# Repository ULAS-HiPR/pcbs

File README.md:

# pcbs
Collection of all HiPR's PCB designs

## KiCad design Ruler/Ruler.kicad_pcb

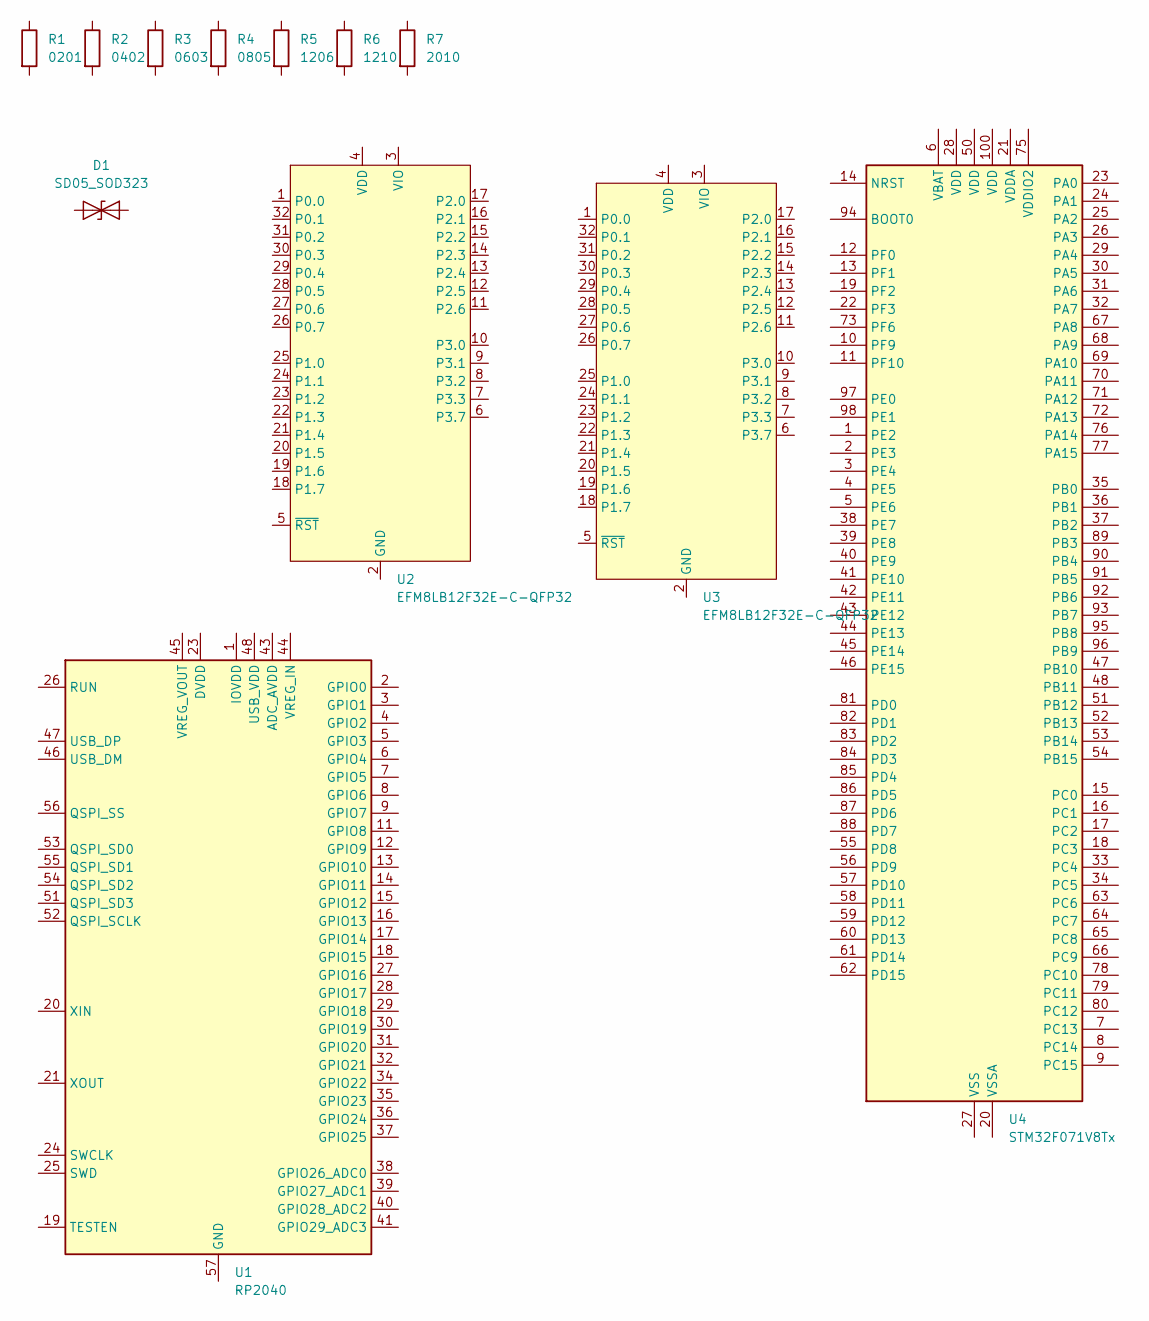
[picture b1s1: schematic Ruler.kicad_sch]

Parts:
D1: SD05_SOD323; D_SOD-323
R1: 0201; R_0201_0603Metric
R2: 0402; R_0402_1005Metric
R3: 0603; R_0603_1608Metric
R4: 0805; R_0805_2012Metric
R5: 1206; R_1206_3216Metric
R6: 1210; R_1210_3225Metric
R7: 2010; R_2010_5025Metric
U1: RP2040; QFN-56-1EP_7x7mm_P0.4mm_EP3.2x3.2mm
U2: EFM8LB12F32E-C-QFP32; LQFP-32_7x7mm_P0.8mm
U3: EFM8LB12F32E-C-QFP32; LQFP-32_5x5mm_P0.5mm
U4: STM32F071V8Tx; LQFP-100_14x14mm_P0.5mm

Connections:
unnamed: U1.23 (DVDD), U1.50 (DVDD)
unnamed: U1.1 (IOVDD), U1.10 (IOVDD), U1.22 (IOVDD), U1.33 (IOVDD), U1.42 (IOVDD), U1.49 (IOVDD)
unnamed: U4.27 (VSS), U4.49 (VSS), U4.74 (VSS), U4.99 (VSS)

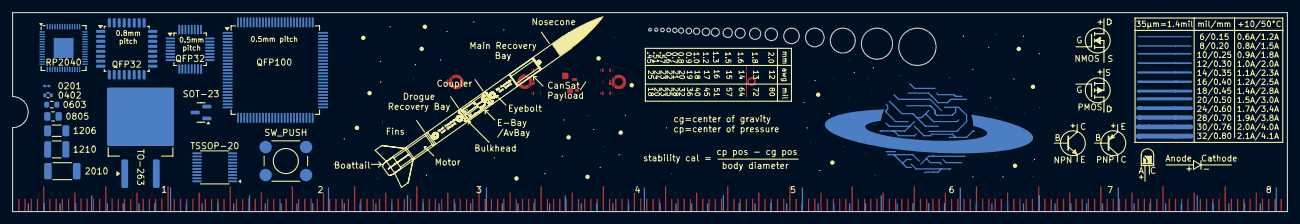
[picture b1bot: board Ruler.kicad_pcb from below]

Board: 2 copper layers, 205.0 x 32.0 mm, 17 parts (17 on the bottom side), 3 nets.

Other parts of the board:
E$50: NMOS-SYMB
E$51: PMOS-SYMB
E$52: DIODE-SYMB
E$53: Val**; LED-GUIDE
E$54: NPN-SYMB
E$59: PNP-SYMB

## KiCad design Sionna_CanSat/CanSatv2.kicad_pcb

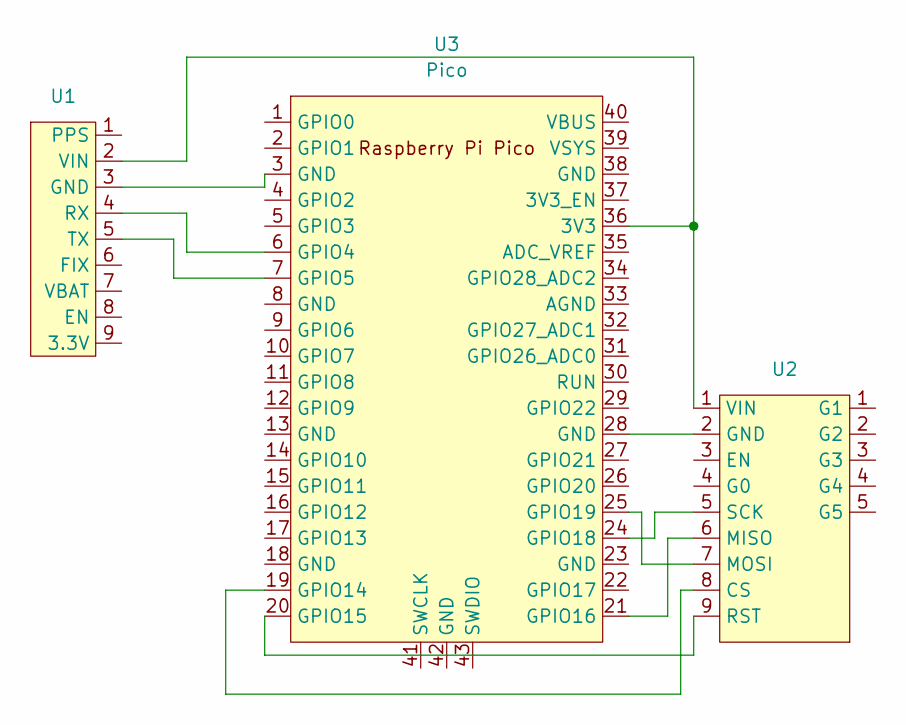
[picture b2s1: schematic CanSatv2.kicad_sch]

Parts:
U1: GPS
U2: LORA
U3: Pico; RPi_Pico_SMD_TH

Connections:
unnamed: U1.3 (GND), U3.3 (GND)
unnamed: U1.4 (RX), U3.6 (GPIO4)
unnamed: U1.5 (TX), U3.7 (GPIO5)
unnamed: U1.2 (VIN), U2.1 (VIN), U3.36 (3V3)
unnamed: U2.8 (CS), U3.19 (GPIO14)
unnamed: U2.2 (GND), U3.28 (GND)
unnamed: U2.6 (MISO), U3.21 (GPIO16)
unnamed: U2.7 (MOSI), U3.25 (GPIO19)
unnamed: U2.9 (RST), U3.20 (GPIO15)
unnamed: U2.5 (SCK), U3.24 (GPIO18)

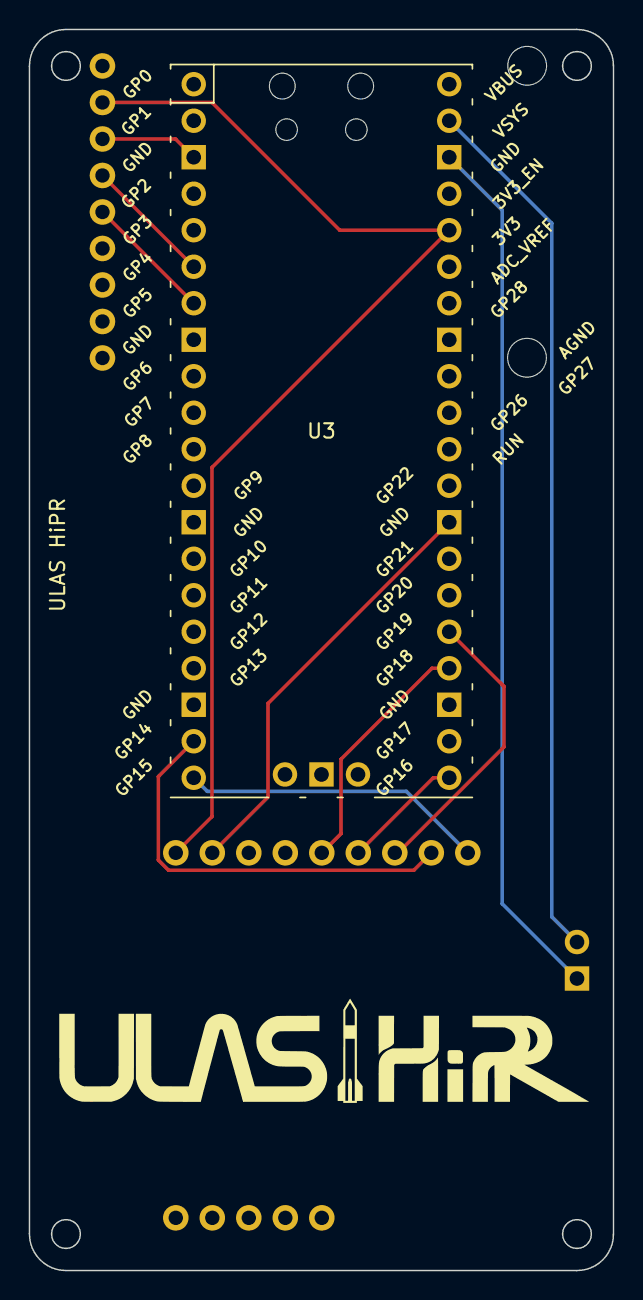
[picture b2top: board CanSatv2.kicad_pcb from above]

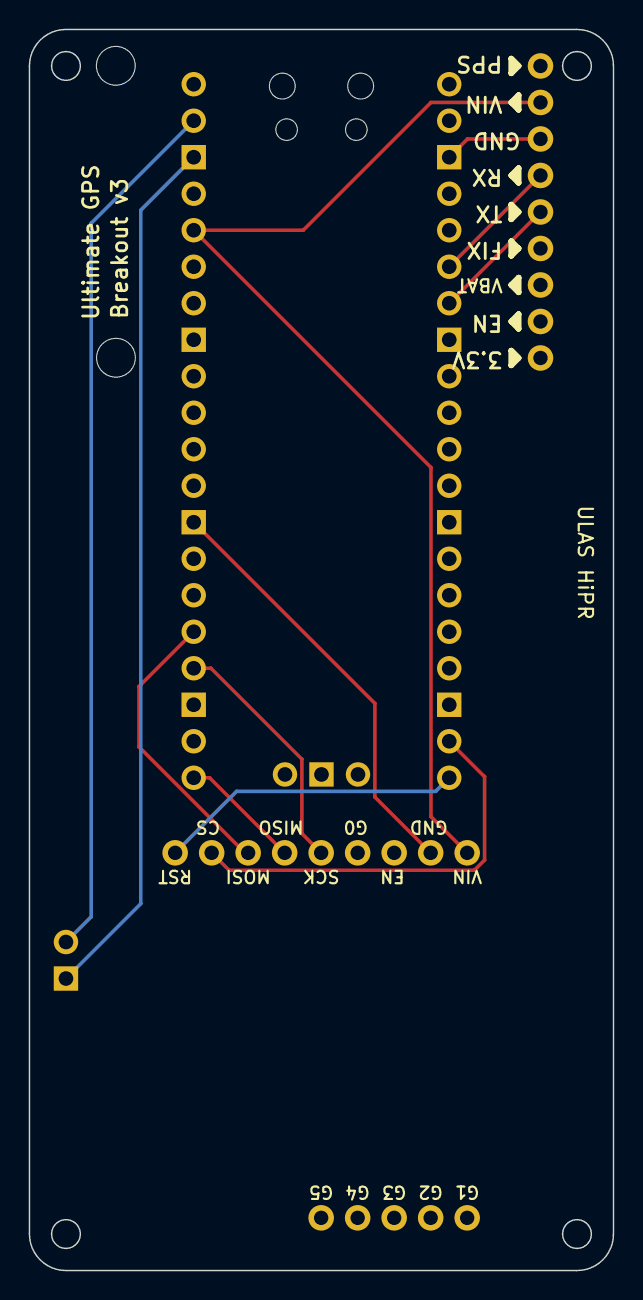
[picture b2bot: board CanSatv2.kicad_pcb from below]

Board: 2 copper layers, 40.6 x 86.4 mm, 3 parts (2 on the bottom side), 10 nets.

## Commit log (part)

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2024-12-21 adding old pcbs
